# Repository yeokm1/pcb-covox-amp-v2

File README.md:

# pcb-covox-amp-v2
A tiny sound card based on the Covox Speech Thing design which includes an LM386 amplifier and FT245RL chip to receive data via USB. This project is a combination of my 2 earlier projects [pcb-covox-amp](https://github.com/yeokm1/pcb-covox-amp) and [pcb-usb-ft245r-parallel-adapter](https://github.com/yeokm1/pcb-usb-ft245r-parallel-adapter)

##PCB Design software and addons used

1. Kicad 4.0.2 or later

##Images

##Schematic drawings

##Parts required
Use Libreoffice to open [pcb-covox-amp-v2-bom.ods](pcb-covox-amp-bom-v2.ods)

##References
1. [Hardware implementation references](https://blog.frantovo.cz/c/307/DAC%20%28zvukov%C3%A1%20karta%29%20pro%20LPT%20port%20a.k.a.%20Covox)
2. [Design reference](http://kb.gr8bit.ru/KB0010/GR8BIT-KB0010-Adding-multimedia-capability-covox-device.html)
3. [MJ-2135 package referenced from coqui-dip](https://github.com/open-eie/coqui-dip)
4. [Amplifier circuit](http://www.circuitbasics.com/build-a-great-sounding-audio-amplifier-with-bass-boost-from-the-lm386/)

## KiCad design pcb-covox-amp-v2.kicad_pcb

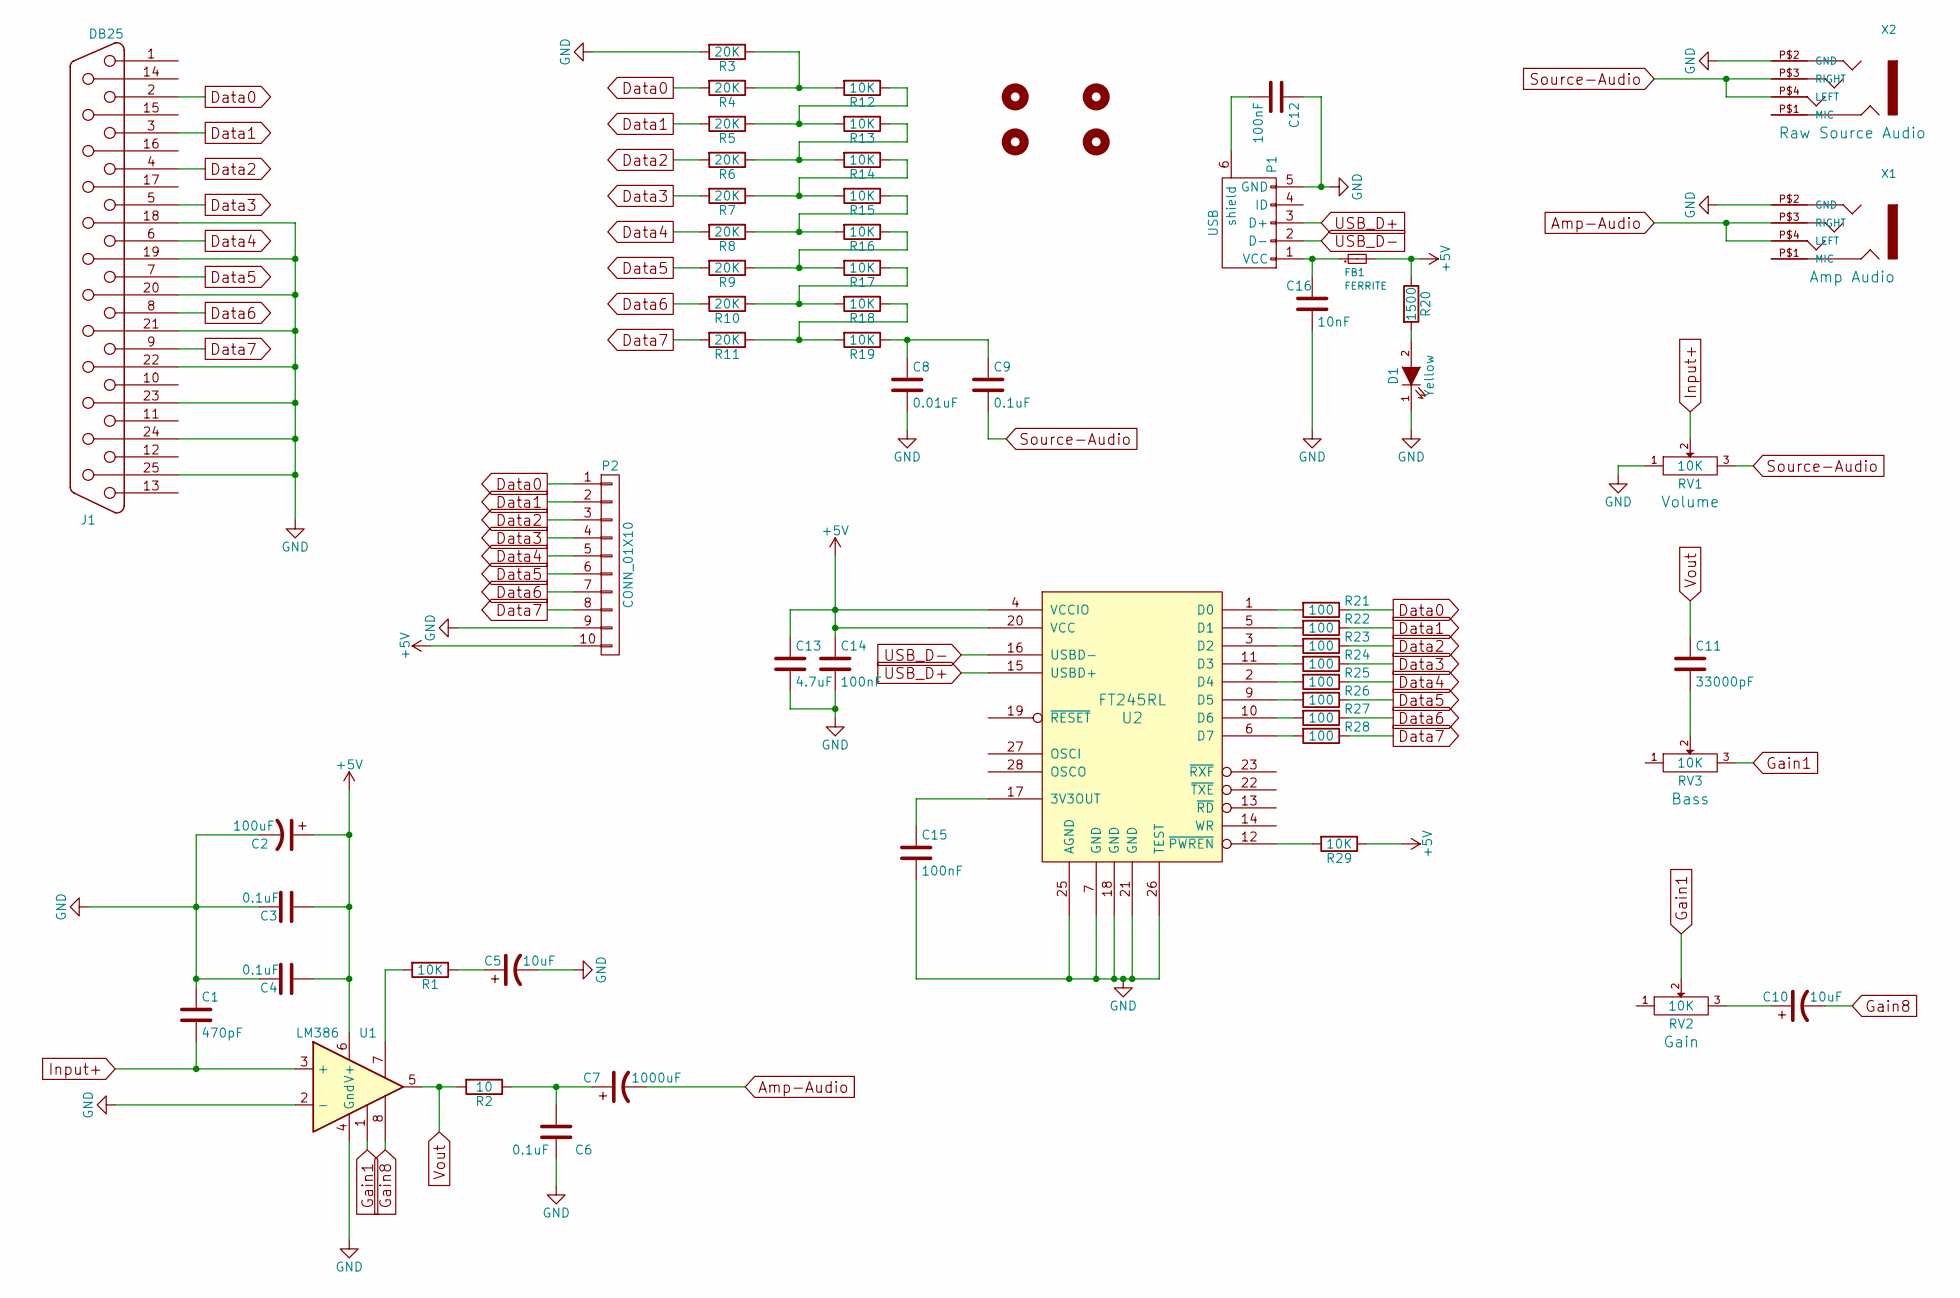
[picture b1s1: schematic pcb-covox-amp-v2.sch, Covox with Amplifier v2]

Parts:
C1: 470pF; C_0805_HandSoldering
C2: 100uF; c_elec_10x10.5
C3, C4, C6, C9: 0.1uF; C_0805_HandSoldering
C5, C10: 10uF; c_elec_4x5.3
C7: 1000uF; c_elec_10x10.5
C8: 0.01uF; C_0805_HandSoldering
C11: 33000pF; C_0805_HandSoldering
C12, C14, C15: 100nF; C_0805_HandSoldering
C13: 4.7uF; C_0805_HandSoldering
C16: 10nF; C_0805_HandSoldering
D1: Yellow; LED_0805
FB1: FERRITE; R_0805_HandSoldering
J1: DB25; DB25MC
MH1, MH2, MH3, MH4: MOUNTHOLE; MountingHole_3.2mm_M3_ISO14580_Pad
P1: USB; USB_Micro-B
P2: CONN_01X10; Pin_Header_Straight_1x10
R1, R12, R13, R14, R15, R16, R17, R18, R19, R29: 10K; R_0805_HandSoldering
R2: 10; R_0805_HandSoldering
R3, R4, R5, R6, R7, R8, R9, R10, R11: 20K; R_0805_HandSoldering
R20: 1500; R_0805_HandSoldering
R21, R22, R23, R24, R25, R26, R27, R28: 100; R_0805_HandSoldering
RV1, RV2, RV3: 10K; Potentiometer_Alps-RK163-single_15mm
U1: LM386; SOIC-8_3.9x4.9mm_Pitch1.27mm
U2: FT245RL; SSOP-28_5.3x10.2mm_Pitch0.65mm
X1: Amp; mj-2135-MJ-2135
X2: Raw; mj-2135-MJ-2135

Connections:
+5V: C2.1, C3.1, C4.1, C13.1, C14.1, FB1.2, P2.10, R20.1, R29.1, U1.6 (V+), U2.4 (VCCIO), U2.20 (VCC)
Amp-Audio: C7.2, X1.P$3 (RIGHT), X1.P$4 (LEFT), X1.P$5 (LEFT)
Data0: J1.2, P2.1, R4.2, R21.1
Data1: J1.3, P2.2, R5.2, R22.1
Data2: J1.4, P2.3, R6.2, R23.1
Data3: J1.5, P2.4, R7.2, R24.1
Data4: J1.6, P2.5, R8.2, R25.1
Data5: J1.7, P2.6, R9.2, R26.1
Data6: J1.8, P2.7, R10.2, R27.1
Data7: J1.9, P2.8, R11.2, R28.1
GND: C1.1, C2.2, C3.2, C4.2, C5.2, C6.2, C8.2, C12.1, C13.2, C14.2, C15.2, C16.2, D1.1 (K), J1.18, J1.19, J1.20, J1.21, J1.22, J1.23, J1.24, J1.25, P1.5 (GND), P2.9, R3.2, RV1.1, U1.2 (-), U1.4 (Gnd), U2.7 (GND), U2.18 (GND), U2.21 (GND), U2.25 (AGND), U2.26 (TEST), X1.P$2 (GND), X2.P$2 (GND)
Gain1: RV2.2, RV3.3, U1.1
Gain8: C10.2, U1.8
Input+: C1.2, RV1.2, U1.3 (+)
unnamed: C5.1, R1.1
unnamed: C6.1, C7.1, R2.1
unnamed: C8.1, C9.1, R19.1
unnamed: C10.1, RV2.3
unnamed: C11.2, RV3.2
unnamed: C12.2, P1.6 (shield)
unnamed: C15.1, U2.17 (3V3OUT)
unnamed: C16.1, FB1.1, P1.1 (VCC)
unnamed: D1.2 (A), R20.2
unnamed: R1.2, U1.7
unnamed: R10.1, R17.1, R18.2
unnamed: R11.1, R18.1, R19.2
unnamed: R5.1, R12.1, R13.2
unnamed: R3.1, R4.1, R12.2
unnamed: R6.1, R13.1, R14.2
unnamed: R7.1, R14.1, R15.2
unnamed: R8.1, R15.1, R16.2
unnamed: R9.1, R16.1, R17.2
unnamed: R21.2, U2.1 (D0)
unnamed: R22.2, U2.5 (D1)
unnamed: R23.2, U2.3 (D2)
unnamed: R24.2, U2.11 (D3)
unnamed: R25.2, U2.2 (D4)
unnamed: R26.2, U2.9 (D5)
unnamed: R27.2, U2.10 (D6)
unnamed: R28.2, U2.6 (D7)
unnamed: R29.2, U2.12 (~PWREN)
Source-Audio: C9.2, RV1.3, X2.P$3 (RIGHT), X2.P$4 (LEFT), X2.P$5 (LEFT)
USB_D+: P1.3 (D+), U2.15 (USBD+)
USB_D-: P1.2 (D-), U2.16 (USBD-)
Vout: C11.1, R2.2, U1.5

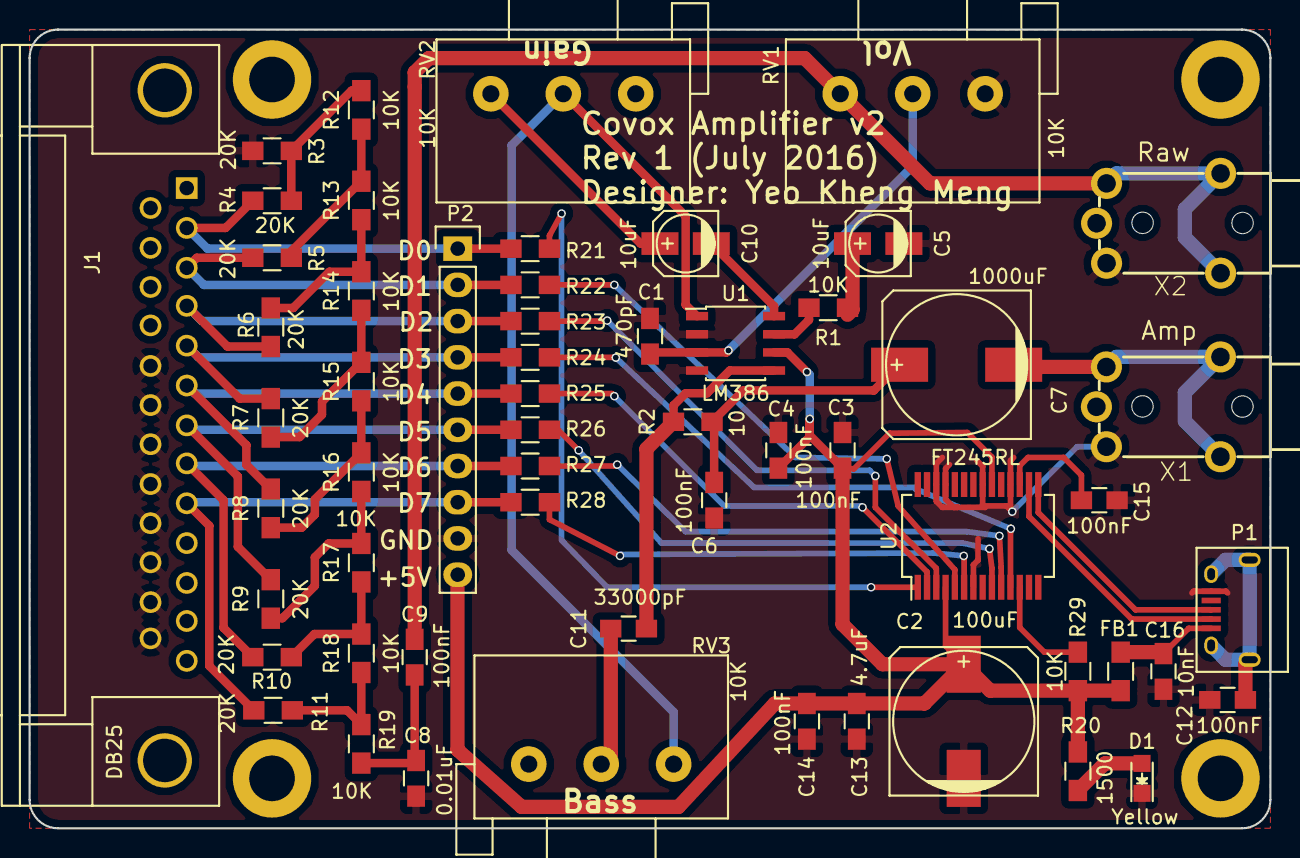
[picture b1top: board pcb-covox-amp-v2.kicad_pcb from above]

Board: 2 copper layers, 87.0 x 56.0 mm, 61 parts (0 on the bottom side), 45 nets.

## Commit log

2016-07-24 another commit
2016-07-25 silkscreen
2016-07-25 gerber
2016-07-25 updated gerber
2016-07-25 add missing libraries
2016-08-02 board image
2016-08-02 updated bom
2016-09-27 update bom column name to value
